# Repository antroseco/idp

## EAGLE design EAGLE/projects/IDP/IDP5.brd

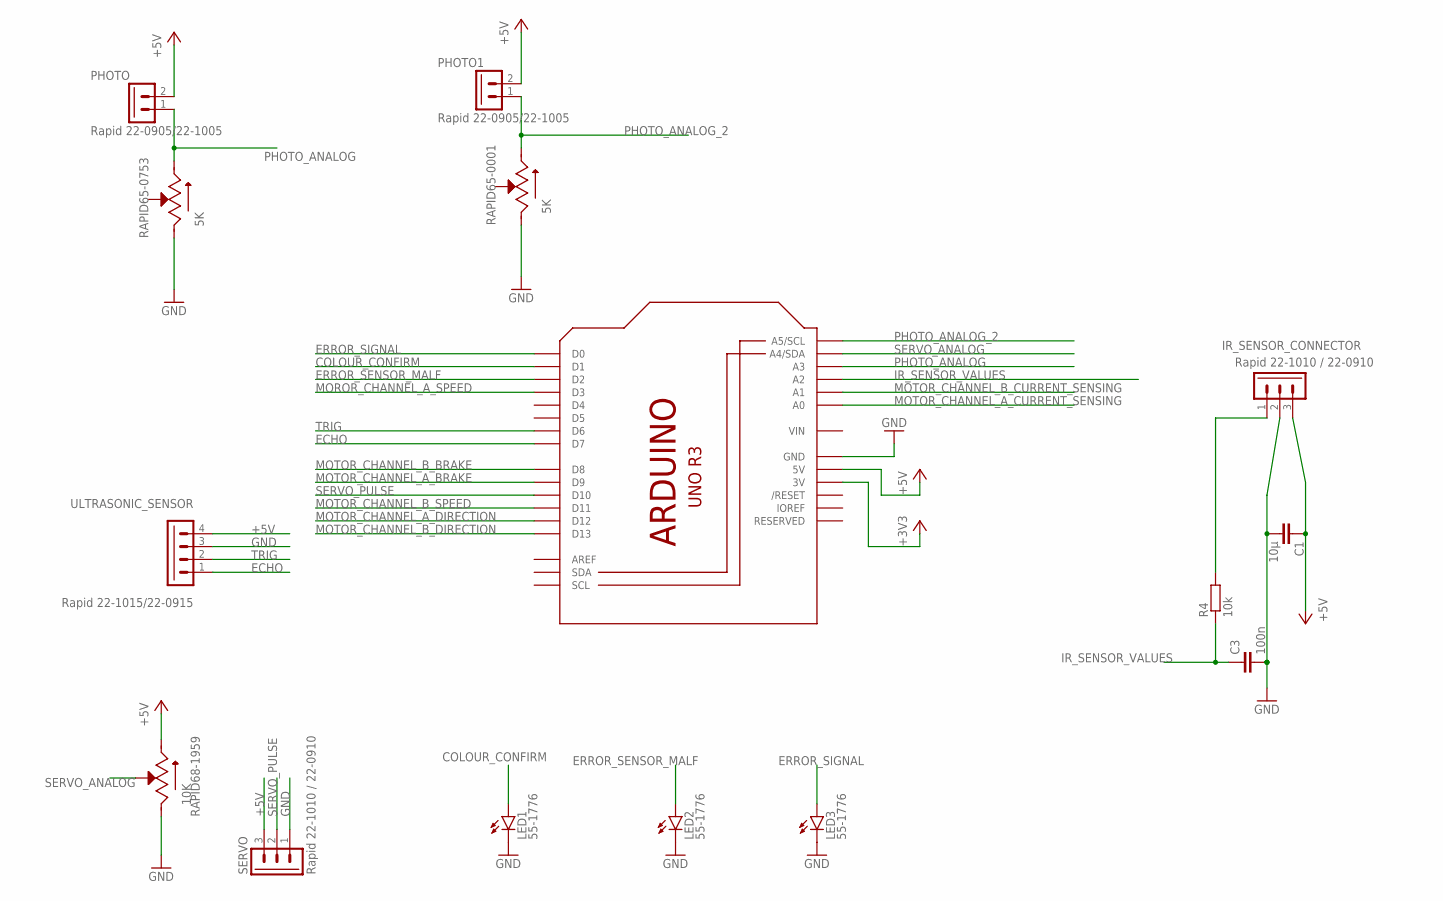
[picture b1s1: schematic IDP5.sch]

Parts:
C1: 10μ; C025-024X044
C3: 100n; C025-024X044
IR_SENSOR_CONNECTOR: Rapid 22-1010 / 22-0910; 7395-03
LED1, LED2, LED3: 55-1776; LED3MM
M1: IDP_PROTOBOARD; IDP_PROTO
PHOTO, PHOTO1: Rapid 22-0905/22-1005; 7395-02
R4: 10k; 0204/7
RAPID65-0001, RAPID65-0753: 5K; TRIM_3296W-1-250
RAPID68-1959: 10K; TRIM_3296W-1-250
SERVO: Rapid 22-1010 / 22-0910; 7395-03
ULTRASONIC_SENSOR: Rapid 22-1015/22-0915; 7395-04

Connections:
+3V3: M1.3V
+5V: C1.1, IR_SENSOR_CONNECTOR.3, M1.5V, M1.5V@0 (5V), M1.5V@1 (5V), M1.5V@2 (5V), M1.5V@3 (5V), M1.5V@4 (5V), M1.5V@5 (5V), M1.5V@6 (5V), M1.5V@7 (5V), M1.5V@8 (5V), M1.5V@9 (5V), M1.5V@10 (5V), M1.5V@11 (5V), M1.5V@12 (5V), M1.5V@13 (5V), M1.5V@14 (5V), M1.5V@15 (5V), M1.5V@16 (5V), M1.5V@17 (5V), M1.5V@18 (5V), M1.5V@19 (5V), M1.5V@20 (5V), M1.5V@21 (5V), M1.5V@22 (5V), M1.5V@23 (5V), M1.5V@24 (5V), M1.5V@25 (5V), M1.5V@26 (5V), M1.5V@27 (5V), M1.5V@28 (5V), M1.5V@29 (5V), M1.5V@30 (5V), M1.5V@31 (5V), M1.5V@32 (5V), M1.5V@33 (5V), M1.5V@34 (5V), M1.5V@35 (5V), M1.5V@36 (5V), M1.5V@37 (5V), M1.5V@38 (5V), M1.5V@39 (5V), M1.5V@40 (5V), PHOTO.2, PHOTO1.2, RAPID68-1959.3 (CW), SERVO.3, ULTRASONIC_SENSOR.4
COLOUR_CONFIRM: LED1.A, M1.D1
ECHO: M1.D7, ULTRASONIC_SENSOR.1
ERROR_SENSOR_MALF: LED2.A, M1.D2
ERROR_SIGNAL: LED3.A, M1.D0
GND: C1.2, C3.2, IR_SENSOR_CONNECTOR.2, LED1.K (C), LED2.K (C), LED3.K (C), M1.GND, M1.GND16 (GND), M1.GND17 (GND), M1.GND18 (GND), M1.GND19 (GND), M1.GND20 (GND), M1.GND21 (GND), M1.GND22 (GND), M1.GND23 (GND), M1.GND24 (GND), M1.GND25 (GND), M1.GND@1 (GND), M1.GND@2 (GND), M1.GND@3 (GND), M1.GND@4 (GND), M1.GND@5 (GND), M1.GND@6 (GND), M1.GND@7 (GND), M1.GND@8 (GND), M1.GND@9 (GND), M1.GND@10 (GND), M1.GND@11 (GND), M1.GND@12 (GND), M1.GND@13 (GND), M1.GND@14 (GND), M1.GND@15 (GND), M1.GND@26 (GND), M1.GND@27 (GND), M1.GND@28 (GND), M1.GND@29 (GND), M1.GND@30 (GND), M1.GND@31 (GND), M1.GND@32 (GND), M1.GND@33 (GND), M1.GND@34 (GND), M1.GND@35 (GND), M1.GND@36 (GND), M1.GND@37 (GND), M1.GND@38 (GND), M1.GND@39 (GND), M1.GND@40 (GND), M1.GND@41 (GND), M1.GND@42 (GND), M1.GND@43 (GND), M1.GND@44 (GND), M1.GND@45 (GND), M1.GND@46 (GND), M1.GND@47 (GND), M1.GND@48 (GND), RAPID65-0001.1 (CCW), RAPID65-0753.1 (CCW), RAPID68-1959.1 (CCW), SERVO.1, ULTRASONIC_SENSOR.3
IR_SENSOR_VALUES: C3.1, M1.A2, R4.1
MOROR_CHANNEL_A_SPEED: M1.D3
MOTOR_CHANNEL_A_BRAKE: M1.D9
MOTOR_CHANNEL_A_CURRENT_SENSING: M1.A0
MOTOR_CHANNEL_A_DIRECTION: M1.D12
MOTOR_CHANNEL_B_BRAKE: M1.D8
MOTOR_CHANNEL_B_CURRENT_SENSING: M1.A1
MOTOR_CHANNEL_B_DIRECTION: M1.D13
MOTOR_CHANNEL_B_SPEED: M1.D11
unnamed: IR_SENSOR_CONNECTOR.1, R4.2
PHOTO_ANALOG: M1.A3, PHOTO.1, RAPID65-0753.3 (CW)
PHOTO_ANALOG_2: M1.A5 (A5/SCL), PHOTO1.1, RAPID65-0001.3 (CW)
SERVO_ANALOG: M1.A4 (A4/SDA), RAPID68-1959.2 (WIPER)
SERVO_PULSE: M1.D10, SERVO.2
TRIG: M1.D6, ULTRASONIC_SENSOR.2

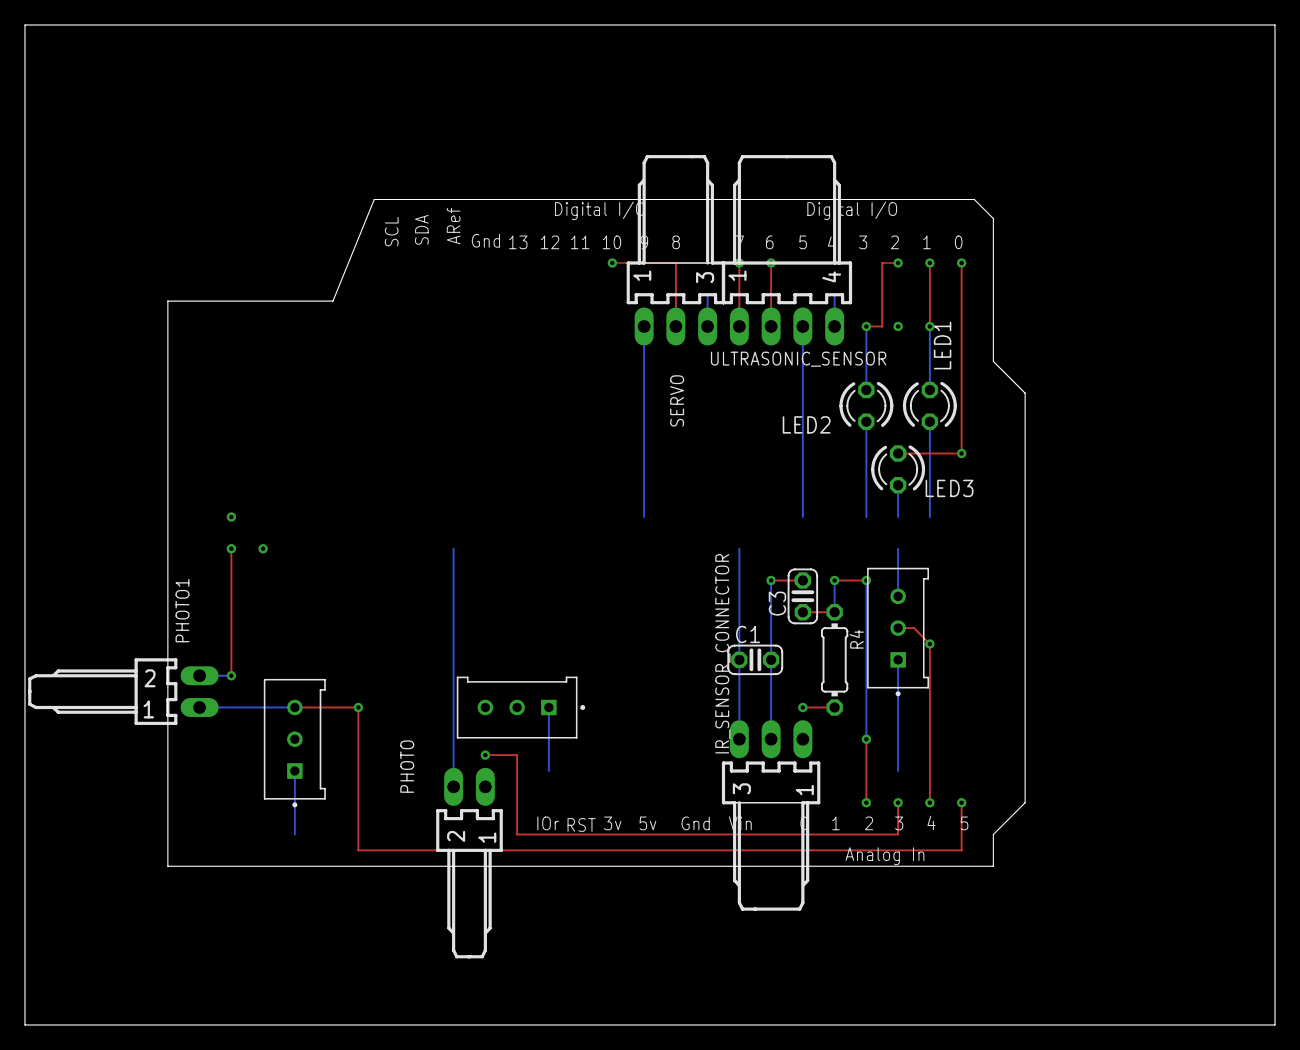
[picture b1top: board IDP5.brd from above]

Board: 2 copper layers, 100.0 x 80.0 mm, 15 parts (0 on the bottom side), 13 nets.

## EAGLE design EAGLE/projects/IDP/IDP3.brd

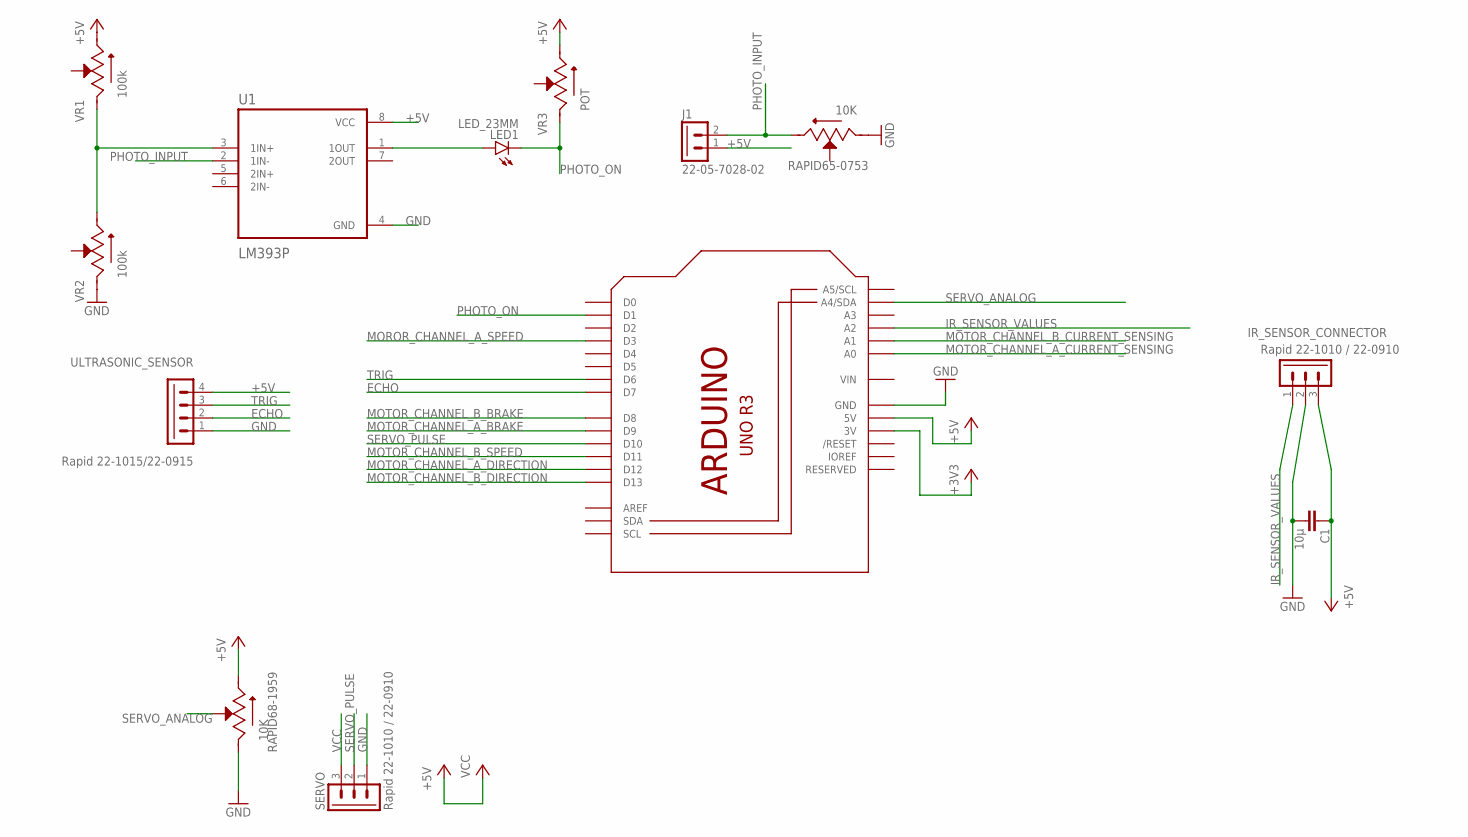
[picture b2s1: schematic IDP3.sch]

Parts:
C1: 10μ; C025-024X044
IR_SENSOR_CONNECTOR: Rapid 22-1010 / 22-0910; 7395-03
J1: 22-05-7028-02; 7395-02
LED1: LED_23MM; LED3MM
M1: IDP_PROTOBOARD; IDP_PROTO
RAPID65-0753, RAPID68-1959: 10K; TRIM_3296W-1-250
SERVO: Rapid 22-1010 / 22-0910; 7395-03
U1: LM393P; DIP794W45P254L959H508Q8
ULTRASONIC_SENSOR: Rapid 22-1015/22-0915; 7395-04
VR1, VR2: 100k; TRIM_3296W-1-250
VR3: POT; TRIM_3296W-1-250

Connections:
+3V3: M1.3V
+5V: C1.1, IR_SENSOR_CONNECTOR.3, J1.1, M1.5V, M1.5V@0 (5V), M1.5V@1 (5V), M1.5V@2 (5V), M1.5V@3 (5V), M1.5V@4 (5V), M1.5V@5 (5V), M1.5V@6 (5V), M1.5V@7 (5V), M1.5V@8 (5V), M1.5V@9 (5V), M1.5V@10 (5V), M1.5V@11 (5V), M1.5V@12 (5V), M1.5V@13 (5V), M1.5V@14 (5V), M1.5V@15 (5V), M1.5V@16 (5V), M1.5V@17 (5V), M1.5V@18 (5V), M1.5V@19 (5V), M1.5V@20 (5V), M1.5V@21 (5V), M1.5V@22 (5V), M1.5V@23 (5V), M1.5V@24 (5V), M1.5V@25 (5V), M1.5V@26 (5V), M1.5V@27 (5V), M1.5V@28 (5V), M1.5V@29 (5V), M1.5V@30 (5V), M1.5V@31 (5V), M1.5V@32 (5V), M1.5V@33 (5V), M1.5V@34 (5V), M1.5V@35 (5V), M1.5V@36 (5V), M1.5V@37 (5V), M1.5V@38 (5V), M1.5V@39 (5V), M1.5V@40 (5V), RAPID68-1959.3 (CW), U1.8 (VCC), ULTRASONIC_SENSOR.4, VR1.3 (CW), VR3.3 (CW)
ECHO: M1.D7, ULTRASONIC_SENSOR.2
GND: C1.2, IR_SENSOR_CONNECTOR.2, M1.GND, M1.GND16 (GND), M1.GND17 (GND), M1.GND18 (GND), M1.GND19 (GND), M1.GND20 (GND), M1.GND21 (GND), M1.GND22 (GND), M1.GND23 (GND), M1.GND24 (GND), M1.GND25 (GND), M1.GND@1 (GND), M1.GND@2 (GND), M1.GND@3 (GND), M1.GND@4 (GND), M1.GND@5 (GND), M1.GND@6 (GND), M1.GND@7 (GND), M1.GND@8 (GND), M1.GND@9 (GND), M1.GND@10 (GND), M1.GND@11 (GND), M1.GND@12 (GND), M1.GND@13 (GND), M1.GND@14 (GND), M1.GND@15 (GND), M1.GND@26 (GND), M1.GND@27 (GND), M1.GND@28 (GND), M1.GND@29 (GND), M1.GND@30 (GND), M1.GND@31 (GND), M1.GND@32 (GND), M1.GND@33 (GND), M1.GND@34 (GND), M1.GND@35 (GND), M1.GND@36 (GND), M1.GND@37 (GND), M1.GND@38 (GND), M1.GND@39 (GND), M1.GND@40 (GND), M1.GND@41 (GND), M1.GND@42 (GND), M1.GND@43 (GND), M1.GND@44 (GND), M1.GND@45 (GND), M1.GND@46 (GND), M1.GND@47 (GND), M1.GND@48 (GND), RAPID65-0753.1 (CCW), RAPID68-1959.1 (CCW), SERVO.1, U1.4 (GND), ULTRASONIC_SENSOR.1, VR2.1 (CCW)
IR_SENSOR_VALUES: IR_SENSOR_CONNECTOR.1, M1.A2
MOROR_CHANNEL_A_SPEED: M1.D3
MOTOR_CHANNEL_A_BRAKE: M1.D9
MOTOR_CHANNEL_A_CURRENT_SENSING: M1.A0
MOTOR_CHANNEL_A_DIRECTION: M1.D12
MOTOR_CHANNEL_B_BRAKE: M1.D8
MOTOR_CHANNEL_B_CURRENT_SENSING: M1.A1
MOTOR_CHANNEL_B_DIRECTION: M1.D13
MOTOR_CHANNEL_B_SPEED: M1.D11
unnamed: LED1.A, U1.1 (1OUT)
unnamed: U1.3 (1IN+), VR1.1 (CCW), VR2.3 (CW)
PHOTO_INPUT: J1.2, RAPID65-0753.3 (CW), U1.2 (1IN-)
PHOTO_ON: LED1.K (C), M1.D1, VR3.1 (CCW)
SERVO_ANALOG: M1.A4 (A4/SDA), RAPID68-1959.2 (WIPER)
SERVO_PULSE: M1.D10, SERVO.2
TRIG: M1.D6, ULTRASONIC_SENSOR.3
VCC: SERVO.3

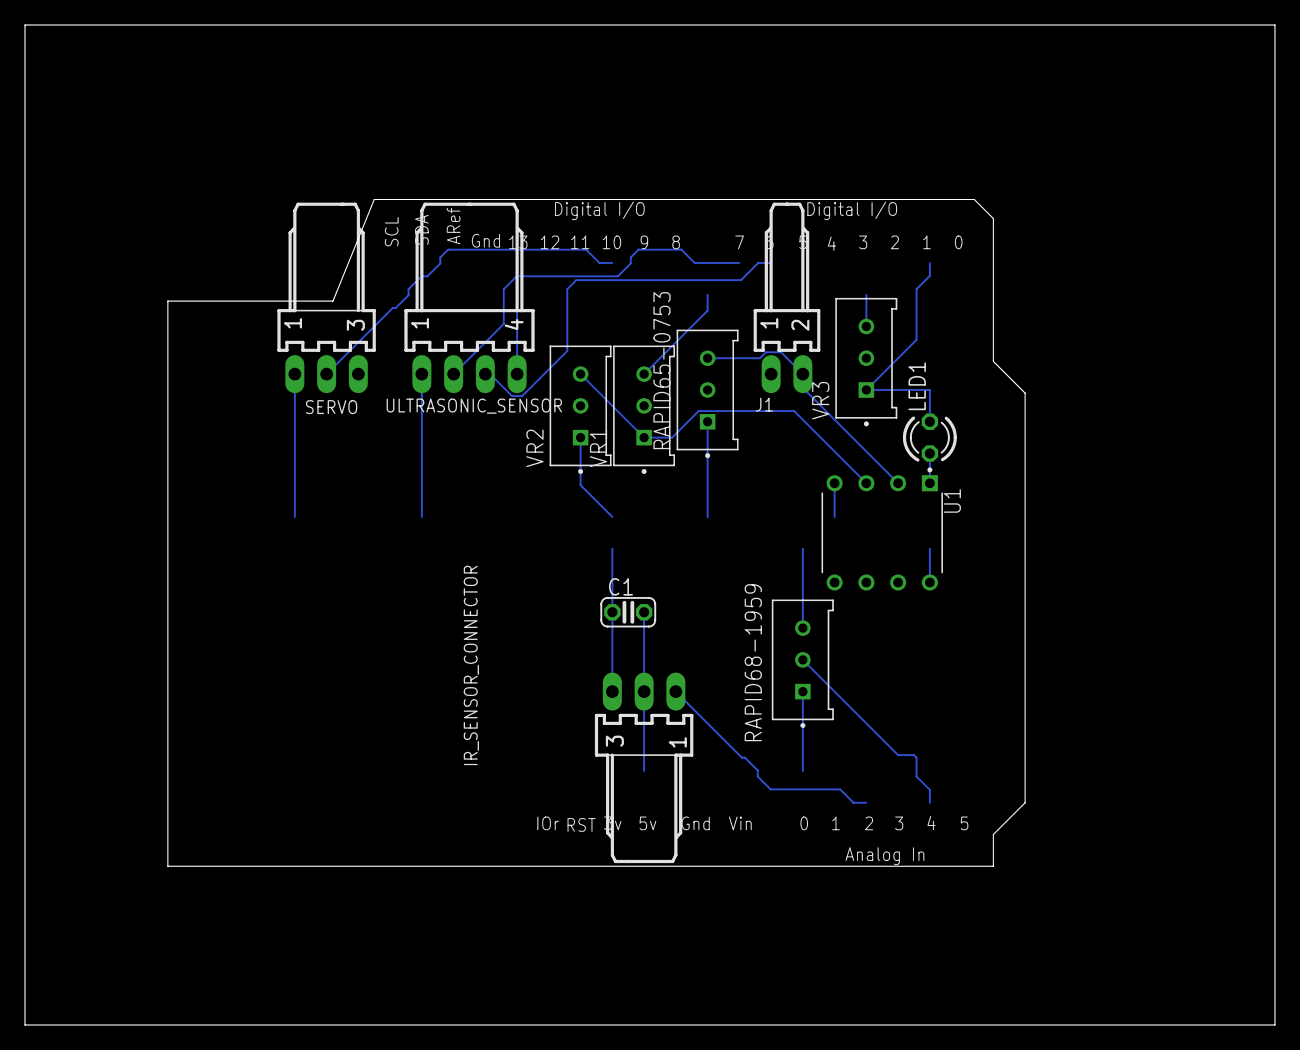
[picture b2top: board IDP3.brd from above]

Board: 2 copper layers, 100.0 x 80.0 mm, 13 parts (0 on the bottom side), 11 nets.

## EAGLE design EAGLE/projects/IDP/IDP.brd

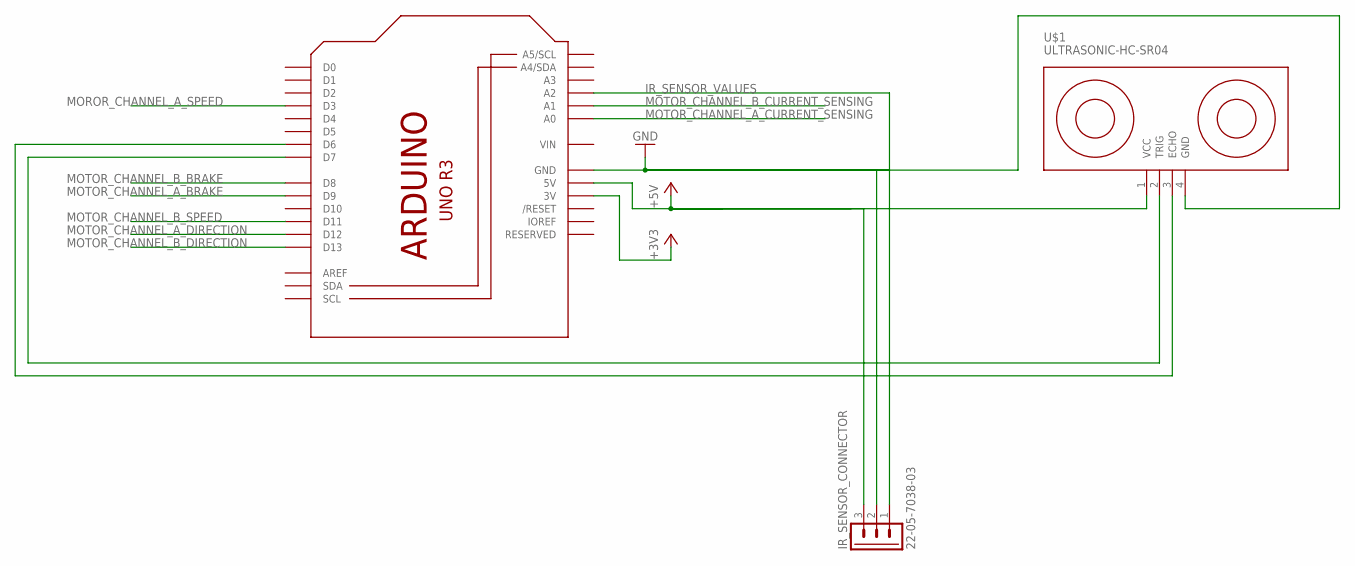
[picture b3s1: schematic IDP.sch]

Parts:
IR_SENSOR_CONNECTOR: 22-05-7038-03; 7395-03
M1: IDP_PROTOBOARD; IDP_PROTO
U$1: ULTRASONIC-HC-SR04

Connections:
+3V3: M1.3V
+5V: IR_SENSOR_CONNECTOR.3, M1.5V, M1.5V@0 (5V), M1.5V@1 (5V), M1.5V@2 (5V), M1.5V@3 (5V), M1.5V@4 (5V), M1.5V@5 (5V), M1.5V@6 (5V), M1.5V@7 (5V), M1.5V@8 (5V), M1.5V@9 (5V), M1.5V@10 (5V), M1.5V@11 (5V), M1.5V@12 (5V), M1.5V@13 (5V), M1.5V@14 (5V), M1.5V@15 (5V), M1.5V@16 (5V), M1.5V@17 (5V), M1.5V@18 (5V), M1.5V@19 (5V), M1.5V@20 (5V), M1.5V@21 (5V), M1.5V@22 (5V), M1.5V@23 (5V), M1.5V@24 (5V), M1.5V@25 (5V), M1.5V@26 (5V), M1.5V@27 (5V), M1.5V@28 (5V), M1.5V@29 (5V), M1.5V@30 (5V), M1.5V@31 (5V), M1.5V@32 (5V), M1.5V@33 (5V), M1.5V@34 (5V), M1.5V@35 (5V), M1.5V@36 (5V), M1.5V@37 (5V), M1.5V@38 (5V), M1.5V@39 (5V), M1.5V@40 (5V), U$1.1 (VCC)
ECHO: M1.D6, U$1.3 (ECHO)
GND: IR_SENSOR_CONNECTOR.2, M1.GND, M1.GND16 (GND), M1.GND17 (GND), M1.GND18 (GND), M1.GND19 (GND), M1.GND20 (GND), M1.GND21 (GND), M1.GND22 (GND), M1.GND23 (GND), M1.GND24 (GND), M1.GND25 (GND), M1.GND@1 (GND), M1.GND@2 (GND), M1.GND@3 (GND), M1.GND@4 (GND), M1.GND@5 (GND), M1.GND@6 (GND), M1.GND@7 (GND), M1.GND@8 (GND), M1.GND@9 (GND), M1.GND@10 (GND), M1.GND@11 (GND), M1.GND@12 (GND), M1.GND@13 (GND), M1.GND@14 (GND), M1.GND@15 (GND), M1.GND@26 (GND), M1.GND@27 (GND), M1.GND@28 (GND), M1.GND@29 (GND), M1.GND@30 (GND), M1.GND@31 (GND), M1.GND@32 (GND), M1.GND@33 (GND), M1.GND@34 (GND), M1.GND@35 (GND), M1.GND@36 (GND), M1.GND@37 (GND), M1.GND@38 (GND), M1.GND@39 (GND), M1.GND@40 (GND), M1.GND@41 (GND), M1.GND@42 (GND), M1.GND@43 (GND), M1.GND@44 (GND), M1.GND@45 (GND), M1.GND@46 (GND), M1.GND@47 (GND), M1.GND@48 (GND), U$1.4 (GND)
IR_SENSOR_VALUES: IR_SENSOR_CONNECTOR.1, M1.A2
MOROR_CHANNEL_A_SPEED: M1.D3
MOTOR_CHANNEL_A_BRAKE: M1.D9
MOTOR_CHANNEL_A_CURRENT_SENSING: M1.A0
MOTOR_CHANNEL_A_DIRECTION: M1.D12
MOTOR_CHANNEL_B_BRAKE: M1.D8
MOTOR_CHANNEL_B_CURRENT_SENSING: M1.A1
MOTOR_CHANNEL_B_DIRECTION: M1.D13
MOTOR_CHANNEL_B_SPEED: M1.D11
TRIG: M1.D7, U$1.2 (TRIG)

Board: 2 copper layers, 3 parts (0 on the bottom side), 5 nets, no tracks yet.

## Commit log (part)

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2021-02-28 Add files via upload
    Robot in world with wheels, claws, ball bearing and sensors modelled, sensors parameters not set yet
2021-02-28 Create testing_git.txt
    Testing git.
2021-02-28 Delete testing_git.txt
    Deleting test file
2021-02-28 Ultrasonic Sensor and Proto
    Finished and can be added to the main robot.
2021-02-28 EAGLE files
2021-02-28 Added sensors, initial robot controller
    Added emitter, receiver, gps and compass to the robot
    Made an initial controller for our robot, just added all of the functions we already wrote
2021-02-28 EAGLE: Add IDP script
2021-02-28 Updated Ultrasonic sensor.
2021-02-28 cache file
2021-02-28 Added Ultrasonic Sensor
2021-02-28 Fix controller
2021-02-28 EAGLE: Add IDP Library
2021-02-28 .gitignore: Ignore .vscode directory
2021-02-28 LTspice Light Detector simulation
2021-03-01 fixed wheel orientation and controller bugs
2021-03-01 initial sweep function
2021-03-01 More LTspice schematics
    Looks like we can't use OpAmps, so just connect it directly to the ADC
    and do all processing in software
2021-03-01 .gitignore: Ignore LTspice simulation files
2021-03-01 Webots: Implement TEPT4400 PROTO file
2021-03-01 Get IR distance sensor values and changed placement of ultrasonic sensor
    The 'beams' of the IR and ultrasonic are now parallel. IR sensor values are also accessible.
2021-03-01 hardware.py: Implement ADC input
2021-03-01 Convert Voltages to Meters on IR Sensor
2021-03-01 hardware.py: Simulate phototransistor circuit
2021-03-01 getting box location, needs fixing
2021-03-01 Robot_controller.py: read Light sensor
2021-03-01 TEPT4400.proto: make sure geomeotry doesn't occlude the sensor
2021-03-01 Add TEPT4400 node
2021-03-01 hardware.py: Fix whitespace
2021-03-01 LightDetector.asc: Modify values
2021-03-01 changed name of IR sensor
2021-03-01 found box positions from a sweep
    working sweep/finding boxes
    will be improved later in the project
2021-03-01 Updating PID_rotation and translation
2021-03-01 Robot_controller.py: fix typo
2021-03-01 Changed bot size to width 20 cm
2021-03-01 Made the Box Claw for the robot, adjusted a few joints
2021-03-01 Added code to control Box Claw
2021-03-02 Finished the Electronics Circuit Diagrams and Layout
2021-03-02 Finishing touches on Frame
2021-03-02 Combined sweep movement and grabbing
    A few issues to be fixed:
    - sometimes box location is estimated to be above 1.2 and the robot gets stuck trying to get there
    - not sure the bounding box of the robot is properly implemented bcs sometimes the box merges with the robot
    - when we put the box in the centre and try to rotate to go elsewhere, we automatically move the box and sometimes even carry it along the way, this needs to be altered
2021-03-02 Include Servo and Change Phototransistor Layout
2021-03-02 Added Part Names
2021-03-02 LTspice: light detector using LM339 comparator
2021-03-02 Transform Analog Phototransistor to Digital and Add LED for Testing
2021-03-03 Update TEPT4400 Webots model
2021-03-03 Update LightDetector w/ Comparator LTspice model
2021-03-03 Implement digital input w/ comparator
2021-03-03 hardware.py: document usage
2021-03-03 Fix type
2021-03-03 Add LTspice model for a light detector w/ EMA
2021-03-03 Add noise to ultrasonic signal
    PID control still works. Noise modelled as standard deviation of 0.002m. No need to remove the noise from ultrasonic signal.
2021-03-04 Add Physics to Robot Body, should behave properly when colliding with walls now.
2021-03-04 Enlarged box claw
2021-03-05 TEPT4000 with red and green filter proto
    Signed-off-by Jerry
2021-03-05 Added BOX_CLAW.proto, use this as endpoint in case we want to use this claw again
2021-03-05 Add SINGLE_CLAW.proto, replace BOX_CLAW with two SINGLE_CLAWs
2021-03-05 Dual—Claw Mechanism Implemented
2021-03-05 upload controller code for controlling claw
2021-03-05 Added code for color detection
2021-03-05 Field set up to try the color detector function
2021-03-06 added a function that tells us where to put the box
    will change this one so that it takes into account the current robot position
2021-03-06 intial collision prevention
2021-03-06 added field class
2021-03-06 added a function that returns the boxes to fields
2021-03-06 added Omar's collision prevention here
2021-03-06 Sending and retrieving location functions
2021-03-06 Add colour filter options to the TEPT4400 PROTO
2021-03-06 Fix typo
2021-03-06 Remove debug output
2021-03-06 Update colour filter transmissivity from datasheets
2021-03-06 Unset TEPT440 boundingObject as physics are disabled
    Silences a Webots warning
2021-03-06 Ignore Webots .cache files
2021-03-06 Right sensor names and protos used
2021-03-06 Added codes for integrating hardware for TEPT with software
2021-03-06 updated controller so that it parks after finishing
2021-03-06 Adjust IR sensor to model voltages before the voltage peak
2021-03-06 Emulate IR quantization noise
2021-03-07 Updated max torque and speeds.
2021-03-08 more work on commmunications
2021-03-08 get and send sweep locations
2021-03-08 both robots working simultaneously, not checking the colours yet
2021-03-08 omar's collision detection
2021-03-08 Re-add maxVelocity and maxTorque fields
2021-03-08 Tune light detector
2021-03-08 field avoidance algoirthm
2021-03-08 Completed Analog Circuit and Back Layout
    Just LEDs are needed to be added.
2021-03-08 Added LED :+1:
2021-03-08 Added low pass filter
2021-03-08 both working together
    problem with speeds and robot collision
2021-03-08 Change Speed
2021-03-08 Update speeds after decreasing req torque.
2021-03-08 64 rpm due to gears
2021-03-09 updated movement and field avoidance
2021-03-09 Agreed dimensions with CAD
2021-03-09 last commit had a bug in .wbt
2021-03-09 changed maxVelocities
2021-03-09 Moved functions to robot.py
2021-03-09 Add remeasuring function
2021-03-09 changed velocities for turning
2021-03-09 documentation and setting max velocity
2021-03-09 Tidied code
2021-03-09 implement remeasure when first attempt fails
2021-03-09 adjusted coefficients for movement and placing boxes
2021-03-09 updated collisions, needs more work
2021-03-10 communication fixed
2021-03-10 adjusted ultrasonic sensor position
2021-03-10 Tuned PID and optimised rotation
2021-03-10 Reverse a bit less
2021-03-10 Sort imports
2021-03-10 Remove dead code (box claw actuation)
2021-03-10 Format code
2021-03-10 added remeasuring the position of the box before sending it to another robot
2021-03-10 Checks the positions in-between the robots
    Takes a valid position even if distance to wall is greater than range. The distance from robot to another robot square measured via webots.
2021-03-10 documentation issues
2021-03-10 Code cleanup
2021-03-10 Don't print measurement result
2021-03-10 Rewrite PID_rotation
2021-03-10 Documented PID_rotation and improved robustness
2021-03-11 Remove unnecessary call to robot.get_messages()
    Already called by robot.step()
2021-03-11 Don't exit after parking
2021-03-11 collisions updated, changed colour of robots
2021-03-11 changed a few parameters, collisions are not always working :((
2021-03-11 final touches
2021-03-11 Patch deploy_dualclaw
2021-03-11 Add TODO
2021-03-12 Trace function calls
2021-03-12 Make bearing and bearing1 static methods
2021-03-12 Remove duplicate definition of TIME_STEP
2021-03-12 Improve bearing functions
    This should be able to handle all edge cases, also code re-use
2021-03-12 deleted first controller
2021-03-12 added capped coordinates near walls
2021-03-13 added function that calculates obstacles on left and right of the robot
2021-03-13 improved collisions
    can be further improved:
    (1) store other robots' bearing as well as position, and move until the way is cleared for the other robot
    (2) if it's possible to turn both left and right, take into account where is the robot currently headed
    (3) also when avoidance happens we need to somehow trigger that in pid_translate function so that it readjusts the angle
2021-03-13 check if it gets stuck while turning
2021-03-13 send bearing along with location
2021-03-13 updated collisions
2021-03-13 3 timesteps PID
2021-03-13 Partially revert "3 timesteps PID"
    This partially reverts commit c85c3f694f7575ba9419ad5c6fef1b0c396a7c51.
    Restore console windows
2021-03-13 Type checking
2021-03-13 Clean up PID_translation
2021-03-13 Add motor helper methods
2021-03-13 Add Robot.move_forwards method
2021-03-13 Use Robot.move_forwards instead of reverse
2021-03-13 Remove duplicate constants
2021-03-13 Remove unnecessary time steps
2021-03-13 Move further away when dropping of a box
2021-03-13 Fix PID_translation when reversing
2021-03-13 Yield when parked
    Fixes a really bad bug
2021-03-13 Accounts for wall and sensor
    Accounts for wall thickness. This allows the boxes in the corners to be found. Also, sensor is actually placed 0.09m from centre of the robot, not 0.11m.
2021-03-13 Short the grab mechanism so it can grab near walls
2021-03-13 Make the robots not detect each other.
2021-03-13 Error rotation lowered since failed to catch blocks far away.
2021-03-13 Single function for claw mechanism, get_target() remeasure now checks according to distance moved instead of steps moved
2021-03-14 PID values for translation
2021-03-14 field collision avoidance tuning
2021-03-14 Fix if statement
2021-03-14 Add collision test cases
2021-03-14 Properly set sensor sampling periods
2021-03-14 Add collision detection to move_forwards
2021-03-14 Tighten move_forwards default threshold
2021-03-14 Update world file
    Red robot gets stuck in the collision prevention algorithm at around 50-60 seconds
2021-03-14 trimmed claw codes
2021-03-14 Debug purpose
2021-03-14 change colour sensor angle
2021-03-14 minor changes in collision
2021-03-14 reverted timestep to 16
2021-03-14 Fixed queue issue
2021-03-15 final collisions (hopefully?)
2021-03-15 restored world file
2021-03-15 Time step measurements 1
2021-03-15 very ugly
2021-03-15 Hmmmm
2021-03-16 Second sweep function.
2021-03-16 Sending updated box locations and new message type
2021-03-16 Merge - sensor measurements every timestep, updating previous box locations. (#2)
    * Time step measurements 1
    * 2
    * 3
    * very ugly
    * Hmmmm
    * Sending updated box locations and new message type
2021-03-16 Consolidate consoles in Webots
2021-03-16 Formatting
2021-03-16 Remove commented out tests
2021-03-16 unique boxes list
2021-03-16 Fix merge and format code
2021-03-16 Improve robot motion
2021-03-16 Changed difference value
2021-03-16 Add more collision test cases
2021-03-16 Remove pointless time step
2021-03-16 Reroute after collision prevention
2021-03-16 Remove all references to Robot.box_queue
2021-03-16 Don't print when rerouting
2021-03-16 FIx double negative
2021-03-17 reroute_after_collision_prevention all the things
2021-03-17 added update_unique_boxes and updated sensor readings at each time step (non working)
2021-03-17 Will only do one sweep after the initial sweep. If no boxes detected, will go back to the parked position.
    Don't know how to make robots go to positions which they found in sweep.
2021-03-17 box collision avoidance
2021-03-17 adjustments to box_collision
2021-03-17 picking up boxes from second sweep
2021-03-17 Rerouting keeps getting better and better
2021-03-17 Remove prints.
2021-03-17 Try and fix reroute again
    This should hopefully eliminate nested calls
2021-03-17 Remove unused import
2021-03-17 second sweep finally done
2021-03-17 box collisions switch
2021-03-17 Fix merge conflicts and format
2021-03-17 Unique_list Solution
2021-03-17 send locations to other robot when done
2021-03-17 Unique_list Solution (#3)
2021-03-17 Add fallback when field is supposed to be full
2021-03-17 Revert "Unique_list Solution (#3)"
    This reverts commit 5396578408040e9e0d3c6a33e1674daa48993ba4.
2021-03-17 Try and fix merge...
2021-03-17 Competition time
2021-03-17 quick fix
2021-03-17 Last minute clean up
2021-03-17 Format
2021-03-21 Final Version
2021-03-21 few changes

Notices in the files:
parts and their libraries:
diy-modules: Released under the Creative Commons Attribution 4.0 International License: http://creativecommons.org/licenses/by/4.0
